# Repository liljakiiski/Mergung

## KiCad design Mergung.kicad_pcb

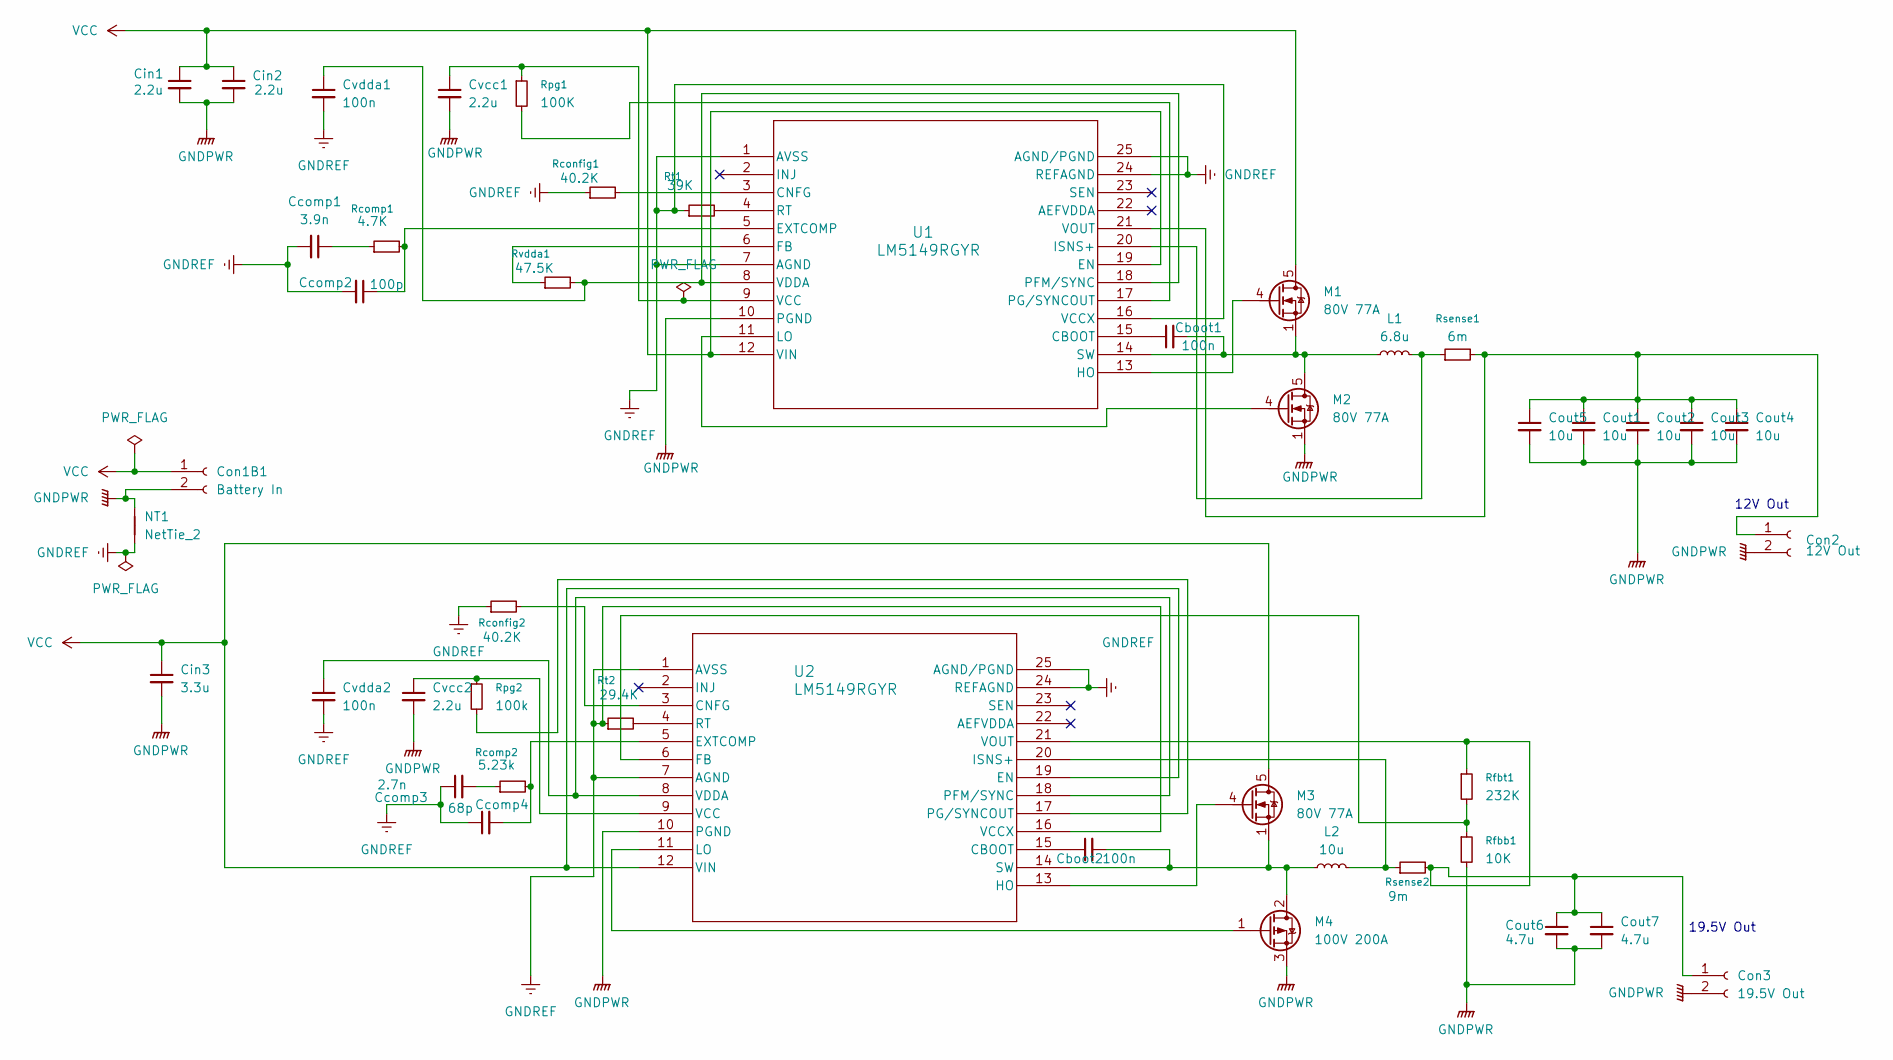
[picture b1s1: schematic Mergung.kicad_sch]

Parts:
Cboot1, Cboot2: 100n; C_0402_1005Metric
Ccomp1: 3.9n; C_0805_2012Metric
Ccomp2: 100p; C_0805_2012Metric
Ccomp3: 2.7n; C_0603_1608Metric
Ccomp4: 68p; C_0805_2012Metric
Cin1, Cin2: 2.2u; C_1210_3225Metric
Cin3: 3.3u; C_1210_3225Metric
Con1B1: Battery In; SolderWirePad_1x01_SMD_5x10mm
Con2: 12V Out; SolderWirePad_1x01_SMD_5x10mm
Con3: 19.5V Out; SolderWirePad_1x01_SMD_5x10mm
Cout1, Cout2, Cout3, Cout4, Cout5: 10u; C_1206_3216Metric
Cout6, Cout7: 4.7u; C_1206_3216Metric
Cvcc1, Cvcc2: 2.2u; C_1210_3225Metric
Cvdda1, Cvdda2: 100n; C_0402_1005Metric
L1: 6.8u; L_Bourns_SRP1245A
L2: 10u; L_Coilcraft_MSS1210-XXX
M1, M2, M3: 80V 77A; TDSON-8-1
M4: 100V 200A; TO-252-2
NT1: NetTie_2; NetTie-2_SMD_Pad2.0mm
Rcomp1: 4.7K; R_0603_1608Metric
Rcomp2: 5.23k; R_0603_1608Metric
Rconfig1, Rconfig2: 40.2K; R_0603_1608Metric
Rfbb1: 10K; R_0603_1608Metric
Rfbt1: 232K; R_0402_1005Metric
Rpg1: 100K; R_0603_1608Metric
Rpg2: 100k; R_0603_1608Metric
Rsense1: 6m; R_1206_3216Metric
Rsense2: 9m; R_1206_3216Metric
Rt1: 39K; R_0402_1005Metric
Rt2: 29.4K; R_0402_1005Metric
Rvdda1: 47.5K; R_0402_1005Metric
U1, U2: LM5149RGYR; VQFN24_RGY_TEX

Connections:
GNDPWR: Cin1.2, Cin2.2, Cin3.2, Con1B1.2, Con2.2, Con3.2, Cout1.2, Cout2.2, Cout3.2, Cout4.2, Cout5.2, Cout6.2, Cout7.2, Cvcc1.2, Cvcc2.2, M2.1 (S), M2.2 (S), M2.3 (S), M4.3 (S), NT1.2, Rfbb1.2, U1.10 (PGND), U2.10 (PGND)
GNDREF: Ccomp1.2, Ccomp2.2, Ccomp3.1, Ccomp4.1, Cvdda1.2, Cvdda2.2, NT1.1, Rconfig1.1, Rconfig2.1, Rt1.1, Rt2.1, U1.1 (AVSS), U1.7 (AGND), U1.16 (VCCX), U1.24 (REFAGND), U1.25 (AGND/PGND), U2.1 (AVSS), U2.7 (AGND), U2.16 (VCCX), U2.24 (REFAGND), U2.25 (AGND/PGND)
unnamed: Ccomp1.1, Rcomp1.1
unnamed: Ccomp3.2, Rcomp2.1
unnamed: Con2.1, Cout1.1, Cout2.1, Cout3.1, Cout4.1, Cout5.1, Rsense1.2, U1.21 (VOUT)
unnamed: Con3.1, Cout6.1, Cout7.1, Rfbt1.1, Rsense2.2, U2.21 (VOUT)
unnamed: M1.4 (G), U1.13 (HO)
unnamed: Cboot1.2, L1.1, M1.1 (S), M1.2 (S), M1.3 (S), M2.5 (D), U1.14 (SW)
unnamed: M2.4 (G), U1.11 (LO)
unnamed: M3.4 (G), U2.13 (HO)
unnamed: Cboot2.2, L2.1, M3.1 (S), M3.2 (S), M3.3 (S), M4.2 (D), U2.14 (SW)
unnamed: M4.1 (G), U2.11 (LO)
unnamed: Cboot1.1, U1.15 (CBOOT)
unnamed: Rconfig1.2, U1.3 (CNFG)
unnamed: Ccomp2.1, Rcomp1.2, U1.5 (EXTCOMP)
unnamed: Rvdda1.1, U1.6 (FB)
unnamed: L1.2, Rsense1.1, U1.20 (ISNS+)
unnamed: Cvdda1.1, Rvdda1.2, U1.8 (VDDA), U1.18 (PFM/SYNC)
unnamed: Rpg1.2, U1.17 (PG/SYNCOUT)
unnamed: Rt1.2, U1.4 (RT)
unnamed: Cvcc1.1, Rpg1.1, U1.9 (VCC)
unnamed: Cboot2.1, U2.15 (CBOOT)
unnamed: Rconfig2.2, U2.3 (CNFG)
unnamed: Ccomp4.2, Rcomp2.2, U2.5 (EXTCOMP)
unnamed: Rfbb1.1, Rfbt1.2, U2.6 (FB)
unnamed: L2.2, Rsense2.1, U2.20 (ISNS+)
unnamed: Cvdda2.1, U2.8 (VDDA), U2.18 (PFM/SYNC)
unnamed: Rpg2.2, U2.17 (PG/SYNCOUT)
unnamed: Rt2.2, U2.4 (RT)
unnamed: Cvcc2.1, Rpg2.1, U2.9 (VCC)
VCC: Cin1.1, Cin2.1, Cin3.1, Con1B1.1, M1.5 (D), M3.5 (D), U1.12 (VIN), U1.19 (EN), U2.12 (VIN), U2.19 (EN)

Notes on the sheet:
19.5V Out
12V Out

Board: 2 copper layers, 45 parts (0 on the bottom side), 31 nets, no tracks yet.

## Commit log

2026-01-28 Initial commit (main file: Mergung)
2026-01-28 ERC errors fixed
2026-02-07 added 1 footprint
2026-02-07 note: wrong footprint for Battery In (temp)
2026-02-07 footprints for vout/vin not here. footprint for lm5149 added.
2026-02-07 new component placement, pending review
